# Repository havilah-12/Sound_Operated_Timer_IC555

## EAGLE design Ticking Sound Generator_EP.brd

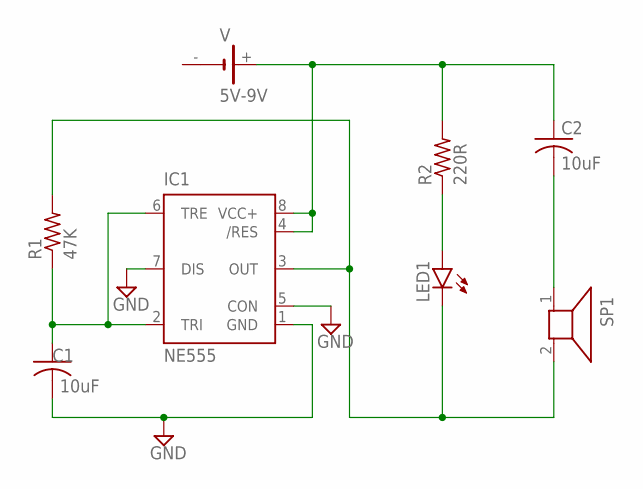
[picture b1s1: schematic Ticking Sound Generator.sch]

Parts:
C1, C2: 10uF; C025-024X044
IC1: NE555; DIL-08
LED1: LAP4-BOTTOM; P47F-BOTTOM
R1: 47K; 0204/7
R2: 220R; 0204/7
SP1: AL23P
V: 5V-9V; SL-150-1/2AA/PT

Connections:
GND: C1.2, IC1.1 (GND), IC1.5 (CON), IC1.7 (DIS)
unnamed: C2.1, IC1.4 (/RES), IC1.8 (VCC+), R2.2, V.+
unnamed: LED1.A, R2.1
unnamed: IC1.3 (OUT), LED1.C, R1.2, SP1.2
unnamed: C2.2, SP1.1
unnamed: C1.1, IC1.2 (TRI), IC1.6 (TRE), R1.1

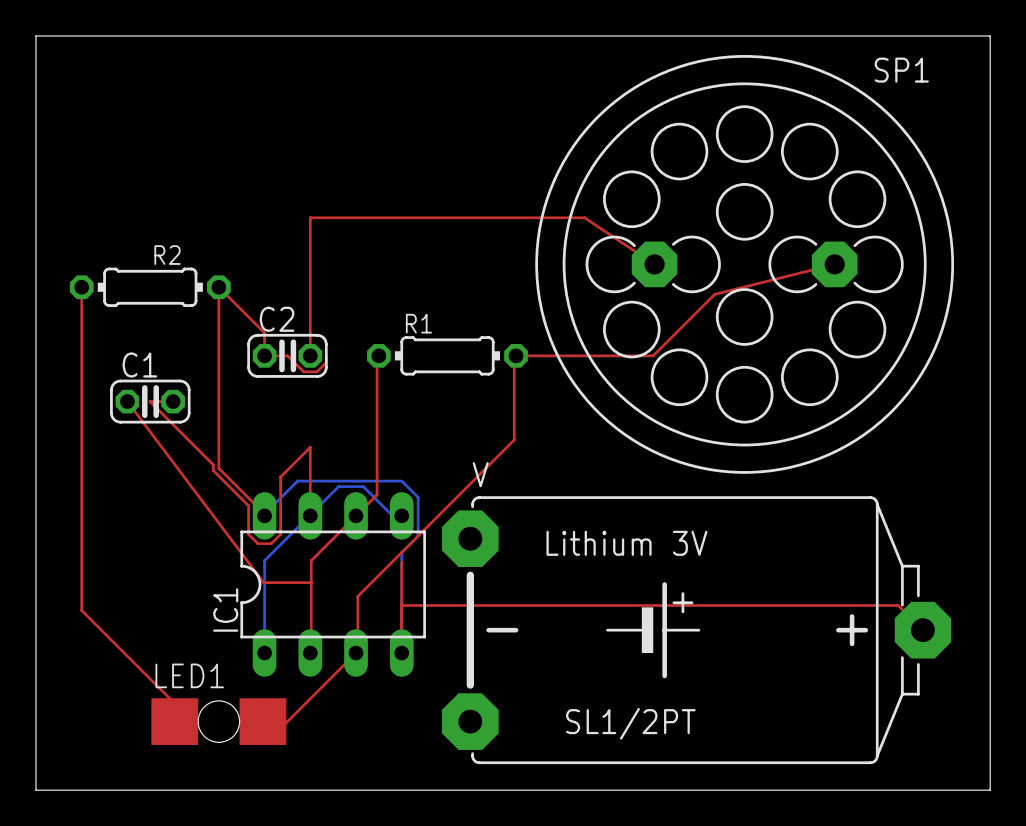
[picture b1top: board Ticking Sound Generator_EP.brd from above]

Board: 2 copper layers, 53.0 x 41.9 mm, 8 parts (0 on the bottom side), 6 nets.
